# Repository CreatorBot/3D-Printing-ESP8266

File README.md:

This LUA code and Adapter for ESP8266 provides wireless networking for RepRap 3D printers. No wired connection is required during the print job - just stream your Gcode up to the ESP module’s IP address.

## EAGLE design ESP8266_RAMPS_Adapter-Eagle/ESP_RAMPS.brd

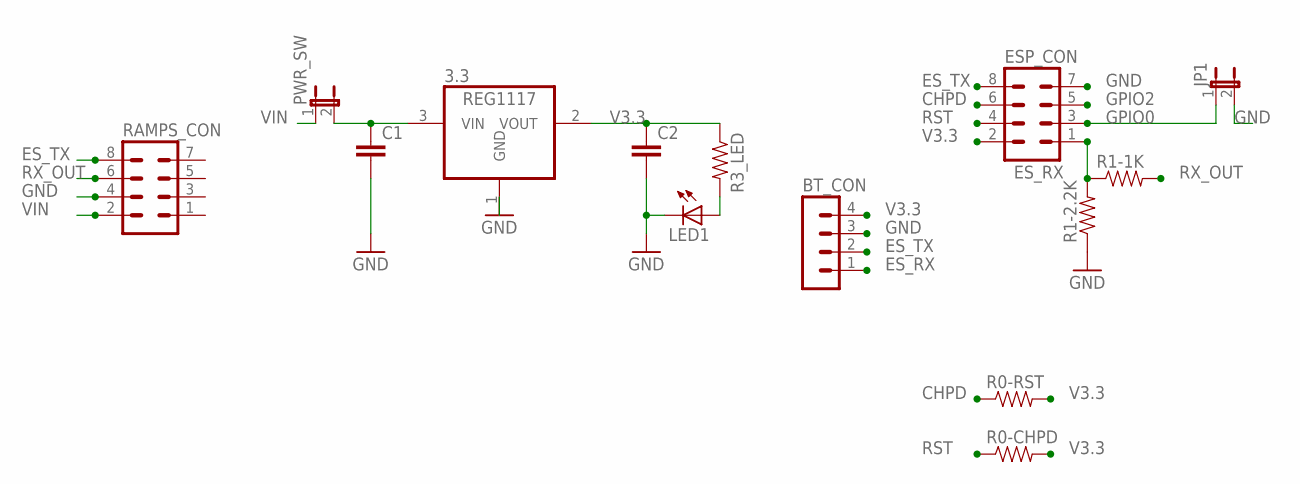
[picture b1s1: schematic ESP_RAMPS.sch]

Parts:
3.3: REG1117; SOT223
BT_CON: MA04-1
C1, C2: CAP1206; 1206
ESP_CON: MA04-2
JP1: JUMPER-2PTH; 1X02
LED1: LED1206; LED-1206
PWR_SW: JUMPER-2PTH; 1X02
R0-CHPD, R0-RST, R1-1K, R1-2.2K, R3_LED: RESISTOR1206; 1206
RAMPS_CON: MA04-2

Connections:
CHPD: ESP_CON.6, R0-RST.1
ES_RX: BT_CON.1, ESP_CON.1, R1-1K.1, R1-2.2K.2
ES_TX: BT_CON.2, ESP_CON.8, RAMPS_CON.8
GND: 3.3.1 (GND), BT_CON.3, C1.2, C2.2, ESP_CON.7, JP1.2, LED1.C, R1-2.2K.1, RAMPS_CON.4
GPIO0: ESP_CON.3, JP1.1
GPIO2: ESP_CON.5
unnamed: LED1.A, R3_LED.2
unnamed: 3.3.3 (VIN), C1.1, PWR_SW.2
RST: ESP_CON.4, R0-CHPD.1
RX_OUT: R1-1K.2, RAMPS_CON.6
V3.3: 3.3.2 (VOUT), BT_CON.4, C2.1, ESP_CON.2, R0-CHPD.2, R0-RST.2, R3_LED.1
VIN: PWR_SW.1, RAMPS_CON.2

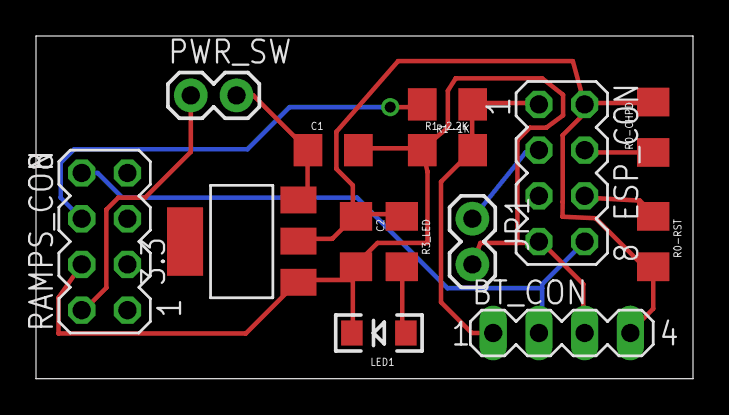
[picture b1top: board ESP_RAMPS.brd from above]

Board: 2 copper layers, 36.5 x 19.0 mm, 14 parts (0 on the bottom side), 11 nets.

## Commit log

2015-04-24 Source Files
